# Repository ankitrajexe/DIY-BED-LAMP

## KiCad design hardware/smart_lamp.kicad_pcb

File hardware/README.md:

# Complete Hardware Design: USB-C Smart Reading Lamp (v2.0)

This directory contains the complete, production-ready KiCad 10 hardware design for the **USB-C Smart Reading Lamp / DIY Bed Lamp**, featuring:
- **KiCad 10 Schematic** (`smart_lamp.kicad_sch`) with **0 ERC errors / 0 warnings**.
- **Complete 2-Layer PCB Layout** (`smart_lamp.kicad_pcb`) with **0 DRC violations / 0 unconnected items**.
- **Photorealistic 3D Renders** (Top & Isometric views).
- **Production Manufacturing Package** (RS-274X Gerbers, Excellon drill files, Bill of Materials, vector PDF schematic).

---

## 1. 3D Board Previews

### Isometric 3D View

### Top View

---

## 2. Hardware Repository Files

| File / Directory | Description |
| :--- | :--- |
| [`smart_lamp.kicad_pro`](file:///c:/DRIVE%20E/MY%20CHORES/DIY%20BED%20LAMP/hardware/smart_lamp.kicad_pro) | KiCad 10 project definition file |
| [`smart_lamp.kicad_sch`](file:///c:/DRIVE%20E/MY%20CHORES/DIY%20BED%20LAMP/hardware/smart_lamp.kicad_sch) | Complete circuit schematic |
| [`smart_lamp.kicad_pcb`](file:///c:/DRIVE%20E/MY%20CHORES/DIY%20BED%20LAMP/hardware/smart_lamp.kicad_pcb) | Fully routed 2-layer PCB layout (85 mm × 60 mm) |
| [`smart_lamp.kicad_sym`](file:///c:/DRIVE%20E/MY%20CHORES/DIY%20BED%20LAMP/hardware/smart_lamp.kicad_sym) | Local project schematic symbol library |
| [`smart_lamp.pretty/`](file:///c:/DRIVE%20E/MY%20CHORES/DIY%20BED%20LAMP/hardware/smart_lamp.pretty/) | Local footprint library (`ESP32-C3-SuperMini.kicad_mod`) |
| [`fp-lib-table`](file:///c:/DRIVE%20E/MY%20CHORES/DIY%20BED%20LAMP/hardware/fp-lib-table) | Footprint library table mapping |
| [`sym-lib-table`](file:///c:/DRIVE%20E/MY%20CHORES/DIY%20BED%20LAMP/hardware/sym-lib-table) | Symbol library table mapping |
| [`gerbers/`](file:///c:/DRIVE%20E/MY%20CHORES/DIY%20BED%20LAMP/hardware/gerbers/) | Complete zip-ready Gerber & Excellon drill fabrication files |
| [`smart_lamp_bom.csv`](file:///c:/DRIVE%20E/MY%20CHORES/DIY%20BED%20LAMP/hardware/smart_lamp_bom.csv) | Full Bill of Materials |
| [`smart_lamp_erc.rpt`](file:///c:/DRIVE%20E/MY%20CHORES/DIY%20BED%20LAMP/hardware/smart_lamp_erc.rpt) | ERC verification report (**0 Errors, 0 Warnings**) |
| [`smart_lamp_drc.rpt`](file:///c:/DRIVE%20E/MY%20CHORES/DIY%20BED%20LAMP/hardware/smart_lamp_drc.rpt) | DRC verification report (**0 Violations, 0 Unconnected**) |
| [`smart_lamp_schematic.pdf`](file:///c:/DRIVE%20E/MY%20CHORES/DIY%20BED%20LAMP/hardware/smart_lamp_schematic.pdf) | High-resolution printable vector schematic PDF |

---

## 3. PCB Layout & Mechanical Specifications

| Parameter | Specification | Notes |
| :--- | :--- | :--- |
| **Dimensions** | 85.0 mm × 60.0 mm | Standard compact desk enclosure form factor |
| **Layer Count** | 2 Layers | Top (`F.Cu`), Bottom (`B.Cu`) |
| **PCB Thickness** | 1.6 mm | Standard FR-4 core |
| **Copper Weight** | 1 oz (35 µm) | Standard outer layer copper |
| **Mounting Holes** | 4× M3 (3.2 mm diameter, 6.0 mm clearance pad) | Inset 3.5 mm from each board corner |
| **Bottom Plane** | Solid GND copper plane | Uninterrupted 0V return path with thermal relief spokes |
| **Minimum Trace / Spacing**| 0.35 mm / 0.25 mm (14 mil / 10 mil) | Standard low-cost fabrication capability |
| **High-Current Traces** | 1.50 mm (60 mil) | +5V Rail, `/LED_WARM_NEG`, `/LED_COOL_NEG` (>3A continuous capability) |
| **Power Distribution Traces** | 0.80 mm / 0.60 mm | 5V MCU feed (0.8mm), +3.3V Sensor/OLED rail (0.6mm) |
| **Signal Traces** | 0.35 mm (14 mil) | PWM outputs, I2C bus (SDA/SCL), Touch in, Page button |

---

## 4. Subsystems & Pinout Mapping

### 4.1 Microcontroller (ESP32-C3 SuperMini)
- **Pin 9 (`5V`)**: 5V DC input filtered by `C1` (100 µF) and `C2` (100 nF).
- **Pin 10 (`GND`)**: Direct tie to solid ground plane.
- **Pin 11 (`3V3`)**: 3.3V regulated output filtered by `C3` (10 µF) and `C4` (100 nF) distributing power to all sensors and OLED.
- **Pin 16 (`GPIO0` / Net `/PWM_WARM`)**: 20 kHz PWM output driving warm white LED MOSFET `Q1`.
- **Pin 15 (`GPIO1` / Net `/PWM_COOL`)**: 20 kHz PWM output driving cool white LED MOSFET `Q2`.
- **Pin 13 (`GPIO3` / Net `/TOUCH_IN`)**: Active-HIGH momentary capacitive touch input from TTP223 module.
- **Pin 12 (`GPIO4` / Net `/I2C_SDA`)**: Hardware I2C data bus with 4.7 kΩ pullup `R5`.
- **Pin 1 (`GPIO5` / Net `/I2C_SCL`)**: Hardware I2C clock bus with 4.7 kΩ pullup `R6`.
- **Pin 2 (`GPIO6` / Net `/BTN_PAGE`)**: Page button input with internal pullup; triggered by onboard tact switch `SW1` or external terminal `J7`.
- **Strapping Pins (`GPIO8`, `GPIO9`)**: Isolated with no-connect markers per `PLAN.md` to prevent bootloader conflicts.

### 4.2 Dual MOSFET Low-Side LED Driver
- **Warm White Channel**:
  - `R1`: 100 Ω damping resistor in series between GPIO0 and `Q1` Gate.
  - `R2`: 10 kΩ pulldown resistor from Gate to GND (ensures MOSFET stays fully off during MCU reset/boot).
  - `Q1`: IRLZ44N logic-level N-channel MOSFET in TO-220 package (Vgs(th) 1.0–2.0V, Rds(on) 22 mΩ at 3.3V).
- **Cool White Channel**:
  - `R3`: 100 Ω damping resistor in series between GPIO1 and `Q2` Gate.
  - `R4`: 10 kΩ pulldown resistor from Gate to GND.
  - `Q2`: IRLZ44N logic-level N-channel MOSFET in TO-220 package.
- **Heat Dissipation**: Both MOSFETs are positioned along the left-center board area with standard TO-220 vertical footprints, accommodating bolt-on clip heatsinks if driving high-power strips (>3A).

### 4.3 Connectors & Peripheral Pinout

| Reference | Component / Function | Footprint | Pinout |
| :--- | :--- | :--- | :--- |
| **J1** | 5V Power Input | TerminalBlock MKDS-1,5 2-Pin | **1:** +5V, **2:** GND |
| **J2** | CCT LED Strip Output | TerminalBlock MKDS-1,5 3-Pin | **1:** +5V (Common Anode), **2:** W- (Warm Cathode), **3:** C- (Cool Cathode) |
| **J3** | SSD1306 0.96" OLED | PinHeader 1x04 (P=2.54mm) | **1:** GND, **2:** +3.3V, **3:** SCL (GPIO5), **4:** SDA (GPIO4) |
| **J4** | DS3231 RTC Module | PinHeader 1x06 (P=2.54mm) | **1:** 32K, **2:** SQW, **3:** SCL, **4:** SDA, **5:** VCC (+3.3V), **6:** GND |
| **J5** | BH1750 Ambient Light Sensor | PinHeader 1x05 (P=2.54mm) | **1:** VCC (+3.3V), **2:** GND, **3:** SCL, **4:** SDA, **5:** ADDR (Tied to GND) |
| **J6** | AHT20 Temperature/Humidity | PinHeader 1x04 (P=2.54mm) | **1:** VIN (+3.3V), **2:** GND, **3:** SCL, **4:** SDA |
| **J7** | External Page Button | PinHeader 1x02 (P=2.54mm) | **1:** BTN_PAGE (GPIO6), **2:** GND |
| **SW1** | Onboard Page Button | Tactile Switch 6x6mm (H=5mm) | **1,2:** BTN_PAGE (GPIO6), **3,4:** GND |
| **MOD1** | TTP223 Touch Module | PinHeader 1x03 (P=2.54mm) | **1:** VCC (+3.3V), **2:** GND, **3:** OUT (GPIO3) |

---

## 5. Bill of Materials (BOM)

| Ref | Value | Package / Footprint | Description | Qty |
| :--- | :--- | :--- | :--- | :---: |
| **U1** | ESP32-C3-SuperMini | PinHeader_2x08_P2.54mm | ESP32-C3 SuperMini MCU module | 1 |
| **Q1, Q2** | IRLZ44N | TO-220-3_Vertical | Logic-Level N-MOSFET (55V, 47A, Vgs(th) 1-2V) | 2 |
| **MOD1** | TTP223_Touch | PinHeader_1x03_P2.54mm | TTP223 capacitive touch sensor module | 1 |
| **SW1** | SW_PUSH_6mm | Button_Switch_THT:SW_PUSH_6mm_H5mm | Onboard momentary page tact switch | 1 |
| **R1, R3** | 100 Ω | Resistor_THT:R_Axial_DIN0207_P7.62mm | 1/4W 5% Metal film gate damping resistor | 2 |
| **R2, R4** | 10 kΩ | Resistor_THT:R_Axial_DIN0207_P7.62mm | 1/4W 5% Metal film gate pulldown resistor | 2 |
| **R5, R6** | 4.7 kΩ | Resistor_THT:R_Axial_DIN0207_P7.62mm | 1/4W 5% Metal film I2C pullup resistor | 2 |
| **C1** | 100 µF 16V | Capacitor_THT:CP_Radial_D6.3mm_P2.50mm | Low-ESR electrolytic bulk filter capacitor | 1 |
| **C2, C4** | 100 nF | Capacitor_THT:C_Disc_D5.0mm_W2.5mm_P5.00mm | Ceramic decoupling capacitor (50V) | 2 |
| **C3** | 10 µF | Capacitor_THT:C_Disc_D5.0mm_W2.5mm_P5.00mm | Ceramic bulk capacitor (16V) | 1 |
| **J1** | 5V_IN | TerminalBlock_Phoenix:MKDS-1,5-2 | 5.08mm 2-pin screw terminal | 1 |
| **J2** | CCT_LED | TerminalBlock_Phoenix:MKDS-1,5-3 | 5.08mm 3-pin screw terminal | 1 |
| **J3, J6** | Conn_01x04 | Connector_PinHeader_2.54mm:PinHeader_1x04_P2.54mm | 4-pin female header (OLED & AHT20) | 2 |
| **J4** | Conn_01x06 | Connector_PinHeader_2.54mm:PinHeader_1x06_P2.54mm | 6-pin female header (DS3231 RTC) | 1 |
| **J5** | Conn_01x05 | Connector_PinHeader_2.54mm:PinHeader_1x05_P2.54mm | 5-pin female header (BH1750 Sensor) | 1 |
| **J7** | Conn_01x02 | Connector_PinHeader_2.54mm:PinHeader_1x02_P2.54mm | 2-pin male header (Ext Page Button) | 1 |
| **H1..H4** | MountingHole_3.2mm_M3 | MountingHole:MountingHole_3.2mm_M3_Pad | M3 mounting holes with 6mm isolation pad | 4 |

---

## 6. Manufacturing & Fabrication Guide

All production files in [`hardware/gerbers/`](file:///c:/DRIVE%20E/MY%20CHORES/DIY%20BED%20LAMP/hardware/gerbers/) adhere to standard RS-274X Gerber and Excellon drill specifications.

### Recommended Fabrication Settings (JLCPCB / PCBWay / Aisler):
- **Base Material**: FR-4 Standard (Tg 130-140°C)
- **Layer Count**: 2 Layers
- **Dimensions**: 85.0 mm × 60.0 mm
- **PCB Thickness**: 1.6 mm
- **Copper Weight**: 1 oz (35 µm)
- **Surface Finish**: HASL with lead (economical) or Lead-Free HASL / ENIG
- **Solder Mask Color**: Matte Black, Blue, or Classic Green
- **Silkscreen Color**: White
- **Minimum Via Diameter / Drill**: 0.8 mm / 0.4 mm

### Gerber Layer Mapping:
- `smart_lamp-F_Cu.gtl` - Top Copper Layer
- `smart_lamp-B_Cu.gbl` - Bottom Copper Layer (GND Plane)
- `smart_lamp-F_Mask.gts` - Top Solder Mask
- `smart_lamp-B_Mask.gbs` - Bottom Solder Mask
- `smart_lamp-F_Silkscreen.gto` - Top Silkscreen Legend
- `smart_lamp-B_Silkscreen.gbo` - Bottom Silkscreen Legend
- `smart_lamp-Edge_Cuts.gm1` - Board Contour & Cutouts (85 mm × 60 mm)
- `smart_lamp.drl` - Excellon Drill File (Plated & Non-Plated Holes)
- `smart_lamp-job.gbrjob` - KiCad Gerber Job Information

---

## 7. Verification Reports Summary

- **ERC Report**: [smart_lamp_erc.rpt](file:///c:/DRIVE%20E/MY%20CHORES/DIY%20BED%20LAMP/hardware/smart_lamp_erc.rpt)
  - **Status**: PASSED (`0 Errors, 0 Warnings`)
- **DRC Report**: [smart_lamp_drc.rpt](file:///c:/DRIVE%20E/MY%20CHORES/DIY%20BED%20LAMP/hardware/smart_lamp_drc.rpt)
  - **Status**: PASSED (`0 DRC Violations, 0 Unconnected Items`)

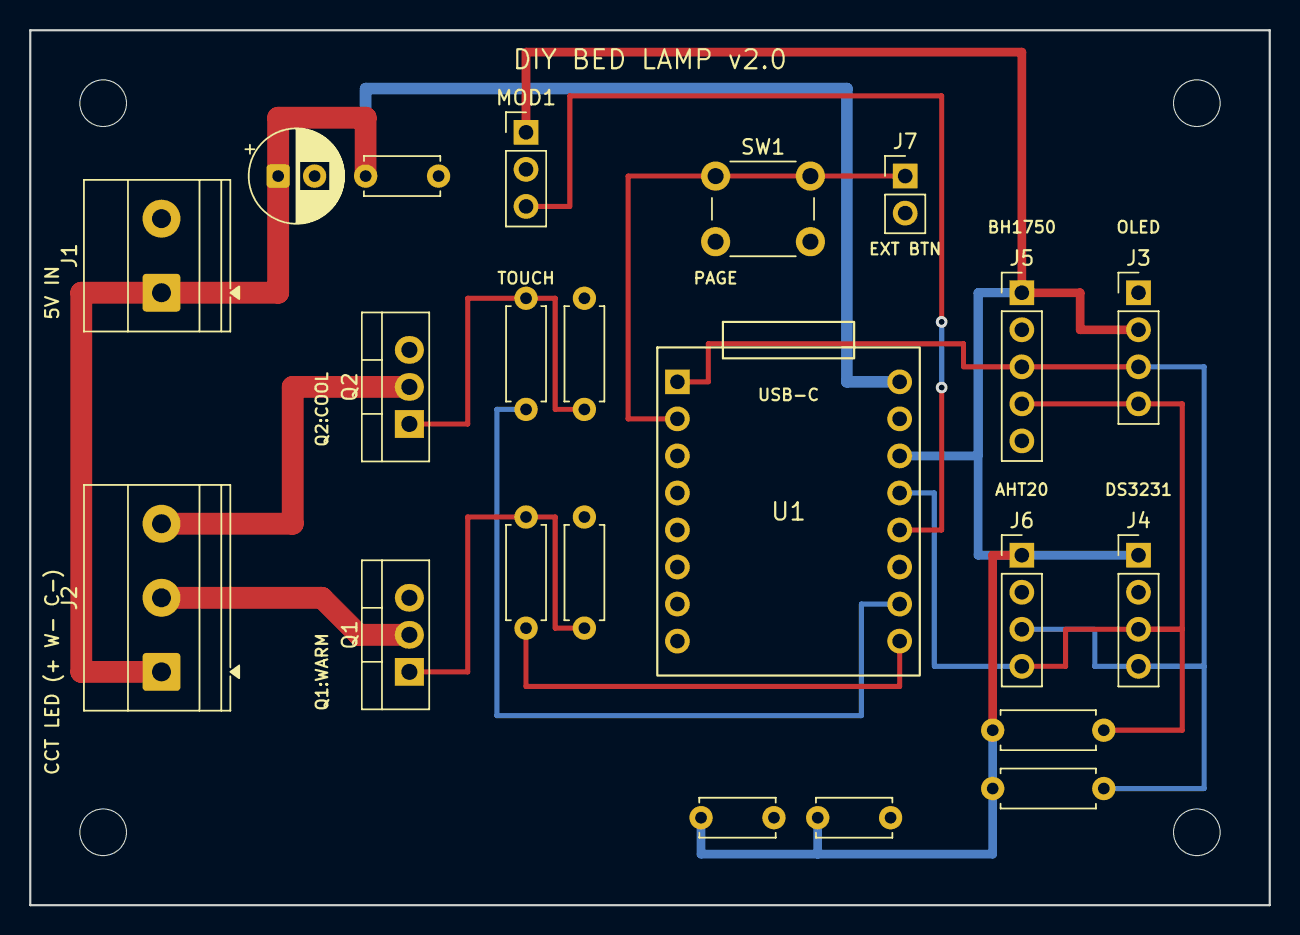
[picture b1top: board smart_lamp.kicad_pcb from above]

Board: 2 copper layers, 85.0 x 60.0 mm, 26 parts (0 on the bottom side), 13 nets.

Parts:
C1: CP_Radial_D6.3mm_P2.50mm
C2, C3, C4: C_Disc_D5.0mm_W2.5mm_P5.00mm
H1, H2, H3, H4: MountingHole_3.2mm_M3
J1: TerminalBlock_Phoenix_MKDS-1,5-2-5.08_1x02_P5.08m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; TerminalBlock_Phoenix_MKDS-1,5-2-5.08_1x02_P5.08mm_Horizont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
J2: TerminalBlock_Phoenix_MKDS-1,5-3-5.08_1x03_P5.08m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; TerminalBlock_Phoenix_MKDS-1,5-3-5.08_1x03_P5.08mm_Horizont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
J3, J4, J6: PinHeader_1x04_P2.54mm_Vertical
J5: PinHeader_1x05_P2.54mm_Vertical
J7: PinHeader_1x02_P2.54mm_Vertical
MOD1: PinHeader_1x03_P2.54mm_Vertical
Q1, Q2: TO-220-3_Vertical
R1, R2, R3, R4, R5, R6: R_Axial_DIN0207_L6.3mm_D2.5mm_P7.62mm_Horizontal
SW1: SW_PUSH_6mm_H5mm
U1: ESP32-C3-SuperMini

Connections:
+3V3: C3.1, C4.1, J3.2, J4.1, J5.1, J6.1, MOD1.1, R5.1, R6.1, U1.11
+5V: C1.1, C2.1, J1.1, J2.1, U1.9
/BTN_PAGE: J7.1, SW1.1, U1.2
/I2C_SCL: J3.3, J4.4, J5.3, J6.3, R6.2, U1.1
/I2C_SDA: J3.4, J4.3, J5.4, J6.4, R5.2, U1.12
/LED_COOL_NEG: J2.3, Q2.2
/LED_WARM_NEG: J2.2, Q1.2
/PWM_COOL: R3.1, U1.15
/PWM_WARM: R1.1, U1.16
/TOUCH_IN: MOD1.3, U1.13
GND: C1.2, C2.2, C3.2, C4.2, J1.2, J3.1, J4.2, J5.2, J5.5, J6.2, J7.2, MOD1.2, Q1.3, Q2.3, R2.2, R4.2, SW1.2, U1.10
unnamed: Q1.1, R1.2, R2.1
unnamed: Q2.1, R3.2, R4.1

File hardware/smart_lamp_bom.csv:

"Refs","Value","Footprint","Qty","DNP"
"C1","100uF_16V","Capacitor_THT:CP_Radial_D6.3mm_P2.50mm","1",""
"C2","100nF","Capacitor_THT:C_Disc_D5.0mm_W2.5mm_P5.00mm","1",""
"C3","10uF","Capacitor_THT:C_Disc_D5.0mm_W2.5mm_P5.00mm","1",""
"C4","100nF","Capacitor_THT:C_Disc_D5.0mm_W2.5mm_P5.00mm","1",""
"H1","MountingHole_M3","MountingHole:MountingHole_3.2mm_M3","1",""
"H2","MountingHole_M3","MountingHole:MountingHole_3.2mm_M3","1",""
"H3","MountingHole_M3","MountingHole:MountingHole_3.2mm_M3","1",""
"H4","MountingHole_M3","MountingHole:MountingHole_3.2mm_M3","1",""
"J1","Conn_01x02_5V_IN","TerminalBlock_Phoenix:TerminalBlock_Phoenix_MKDS-1,5-2-5.08_1x02_P5.08mm_Horizontal","1",""
"J2","Conn_01x03_LED","TerminalBlock_Phoenix:TerminalBlock_Phoenix_MKDS-1,5-3-5.08_1x03_P5.08mm_Horizontal","1",""
"J3","Conn_01x04_OLED","Connector_PinHeader_2.54mm:PinHeader_1x04_P2.54mm_Vertical","1",""
"J4","Conn_01x04_DS3231","Connector_PinHeader_2.54mm:PinHeader_1x04_P2.54mm_Vertical","1",""
"J5","Conn_01x05_BH1750","Connector_PinHeader_2.54mm:PinHeader_1x05_P2.54mm_Vertical","1",""
"J6","Conn_01x04_AHT20","Connector_PinHeader_2.54mm:PinHeader_1x04_P2.54mm_Vertical","1",""
"J7","Conn_01x02_Ext_BTN","Connector_PinHeader_2.54mm:PinHeader_1x02_P2.54mm_Vertical","1",""
"MOD1","TTP223_Touch","Connector_PinHeader_2.54mm:PinHeader_1x03_P2.54mm_Vertical","1",""
"Q1","IRLZ44N","Package_TO_SOT_THT:TO-220-3_Vertical","1",""
"Q2","IRLZ44N","Package_TO_SOT_THT:TO-220-3_Vertical","1",""
"R1","100","Resistor_THT:R_Axial_DIN0207_L6.3mm_D2.5mm_P7.62mm_Horizontal","1",""
"R2","10k","Resistor_THT:R_Axial_DIN0207_L6.3mm_D2.5mm_P7.62mm_Horizontal","1",""
"R3","100","Resistor_THT:R_Axial_DIN0207_L6.3mm_D2.5mm_P7.62mm_Horizontal","1",""
"R4","10k","Resistor_THT:R_Axial_DIN0207_L6.3mm_D2.5mm_P7.62mm_Horizontal","1",""
"R5","4.7k","Resistor_THT:R_Axial_DIN0207_L6.3mm_D2.5mm_P7.62mm_Horizontal","1",""
"R6","4.7k","Resistor_THT:R_Axial_DIN0207_L6.3mm_D2.5mm_P7.62mm_Horizontal","1",""
"SW1","SW_Push","Button_Switch_THT:SW_PUSH_6mm_H5mm","1",""
"U1","ESP32-C3-SuperMini","smart_lamp:ESP32-C3-SuperMini","1",""
